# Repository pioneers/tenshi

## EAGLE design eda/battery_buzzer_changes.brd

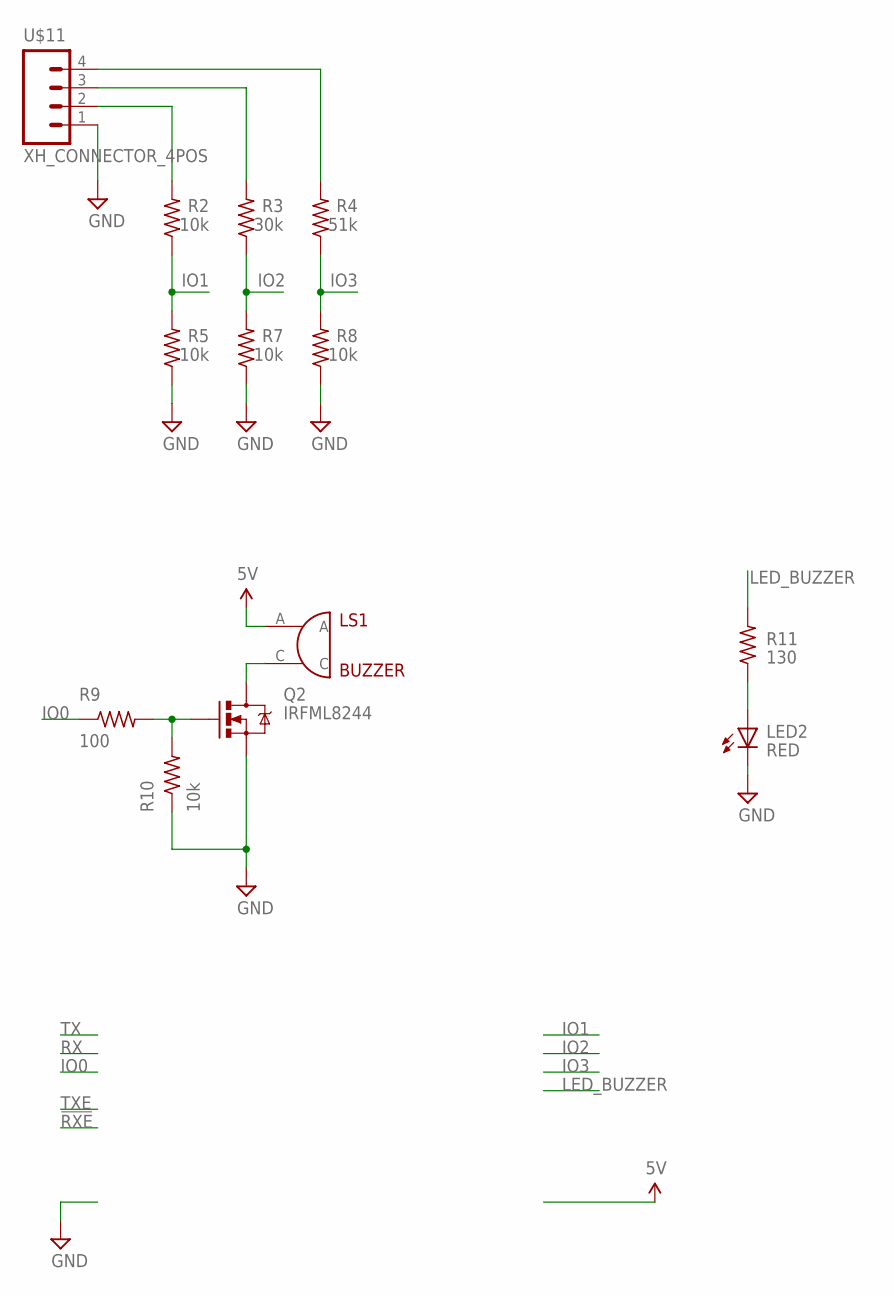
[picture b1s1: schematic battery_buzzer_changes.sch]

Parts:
LED2: RED; LED-0805
LS1: BUZZER; BUZZER_MAGNETIC_5V_12MM_RADIAL
Q2: IRFML8244; SOT23-3
R2, R5, R7, R8, R10: 10k; R0603
R3: 30k; R0603
R4: 51k; R0603
R9: 100; R0603
R11: 130; R0603
U$11: XH_CONNECTOR_4POS; XH_CONNECTOR_4POS_2.5MM

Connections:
5V: LS1.A
GND: LED2.C, Q2.2 (S), R5.1, R7.1, R8.1, R10.1, U$11.1
IO0: R9.1
IO1: R2.1, R5.2
IO2: R3.1, R7.2
IO3: R4.1, R8.2
LED_BUZZER: R11.2
unnamed: R2.2, U$11.2
unnamed: R3.2, U$11.3
unnamed: R4.2, U$11.4
unnamed: LS1.C, Q2.3 (D)
unnamed: Q2.1 (G), R9.2, R10.2
unnamed: LED2.A, R11.1

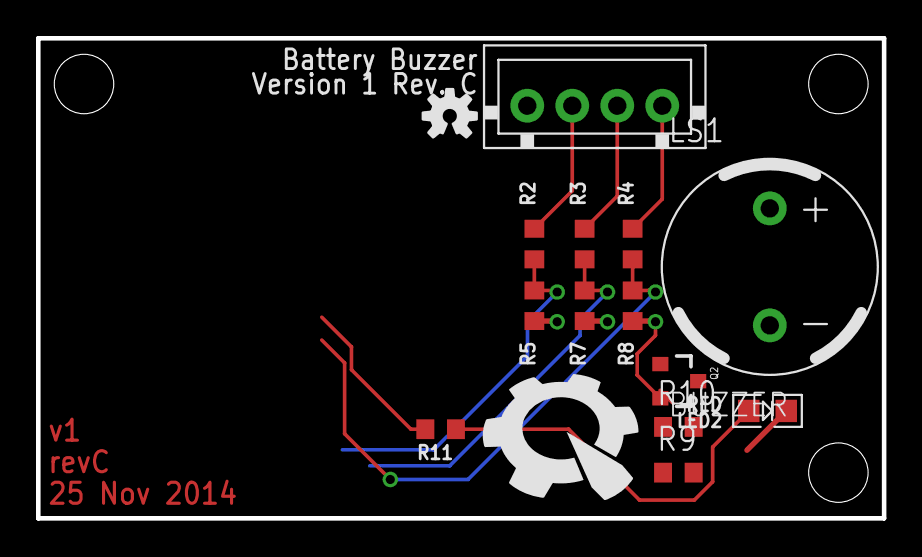
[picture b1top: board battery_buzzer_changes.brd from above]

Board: 2 copper layers, 47.0 x 26.7 mm, 18 parts (0 on the bottom side), 10 nets.

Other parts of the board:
U$1: PIE-LOGO-SMALL
U$7: OSHW-LOGO-S
U$8, U$9, U$17: STAND-OFF

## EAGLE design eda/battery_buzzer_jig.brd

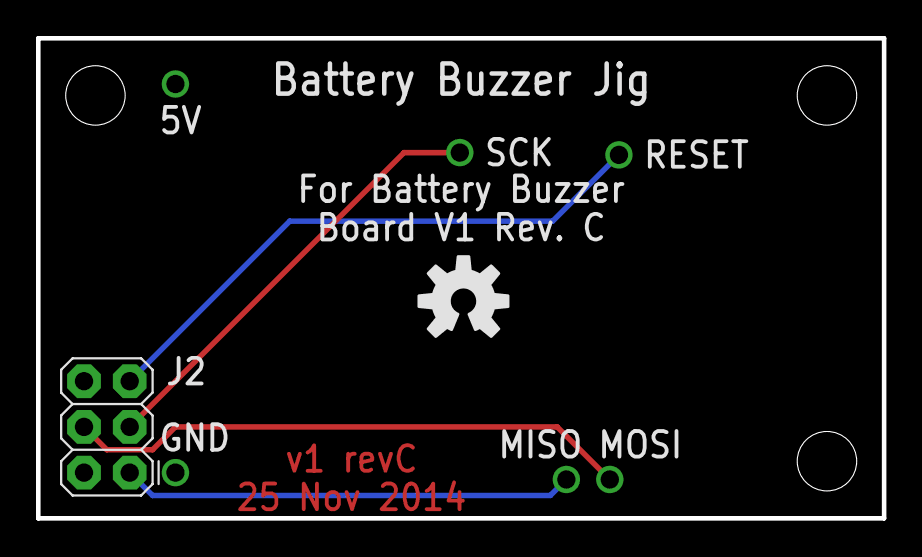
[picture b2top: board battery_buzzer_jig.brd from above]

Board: 2 copper layers, 47.0 x 26.7 mm, 12 parts (1 on the bottom side), 6 nets.

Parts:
5V: POGO_PIN_394
GND: POGO_PIN_394
J2: AVR_SPI_PRG_6PTH; 2X3
MISO: POGO_PIN_394
MOSI: POGO_PIN_394
RESET: POGO_PIN_394
SCK: POGO_PIN_394
U$1: OSHW-LOGO-M
U$2: PIE-LOGO-SMALL
U$3, U$4, U$5: STAND-OFF

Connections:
5V: 5V.POGO_PIN, J2.2
A: GND.POGO_PIN, J2.6
MISO: J2.1, MISO.POGO_PIN
MOSI: J2.4, MOSI.POGO_PIN
RESET: J2.5, RESET.POGO_PIN
SCK: J2.3, SCK.POGO_PIN

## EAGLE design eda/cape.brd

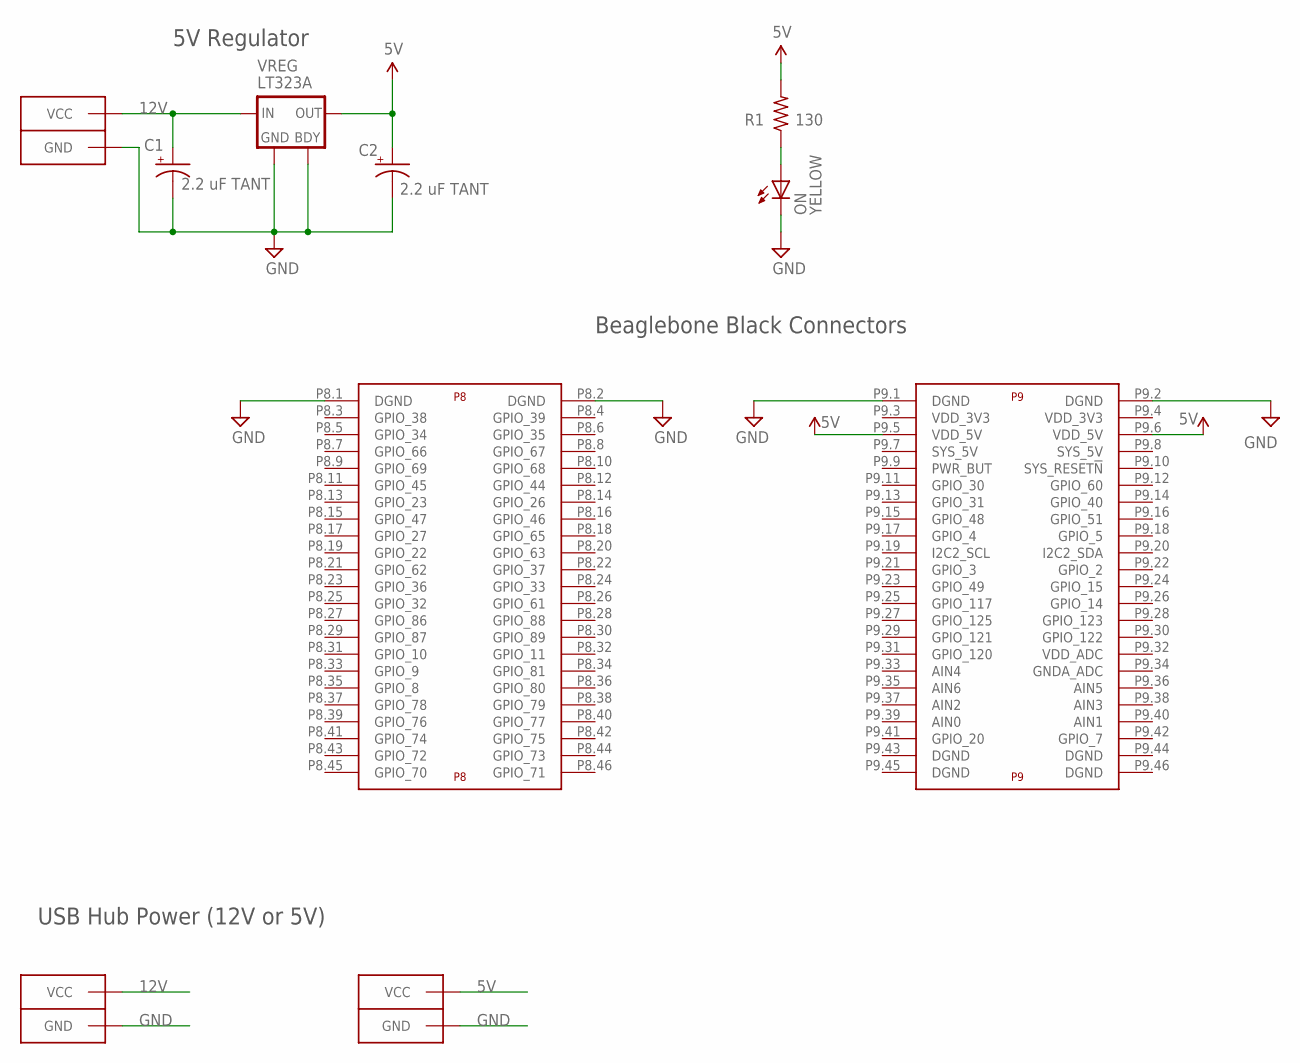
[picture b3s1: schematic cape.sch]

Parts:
BATT: 12V; ANDERSON_HORIZONTAL
C1, C2: 2.2 uF TANT; EIA3216
CAPE: BEAGLE_BONE_BLACK_CAPE
J2: 12V; POWER-WIRE
J3: 5V; POWER-WIRE
ON: YELLOW; LED-0805
R1: 130; R0603
VREG: LT323A; TO-220

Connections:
5V: C2.A (+), CAPE.P9.5 (VDD_5V), CAPE.P9.6 (VDD_5V), J3.VCC, R1.2, VREG.OUT
12V: BATT.PIN2 (VCC), BATT.PIN2-LEAD (VCC), C1.A (+), J2.VCC, VREG.IN
GND: BATT.PIN1 (GND), BATT.PIN1-LEAD (GND), C1.C (-), C2.C (-), CAPE.P8.1 (DGND), CAPE.P8.2 (DGND), CAPE.P9.1 (DGND), CAPE.P9.2 (DGND), J2.GND, J3.GND, ON.C, VREG.GND, VREG.PAD (BDY)
unnamed: ON.A, R1.1

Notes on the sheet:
Beaglebone Black Connectors
USB Hub Power (12V or 5V)
5V Regulator

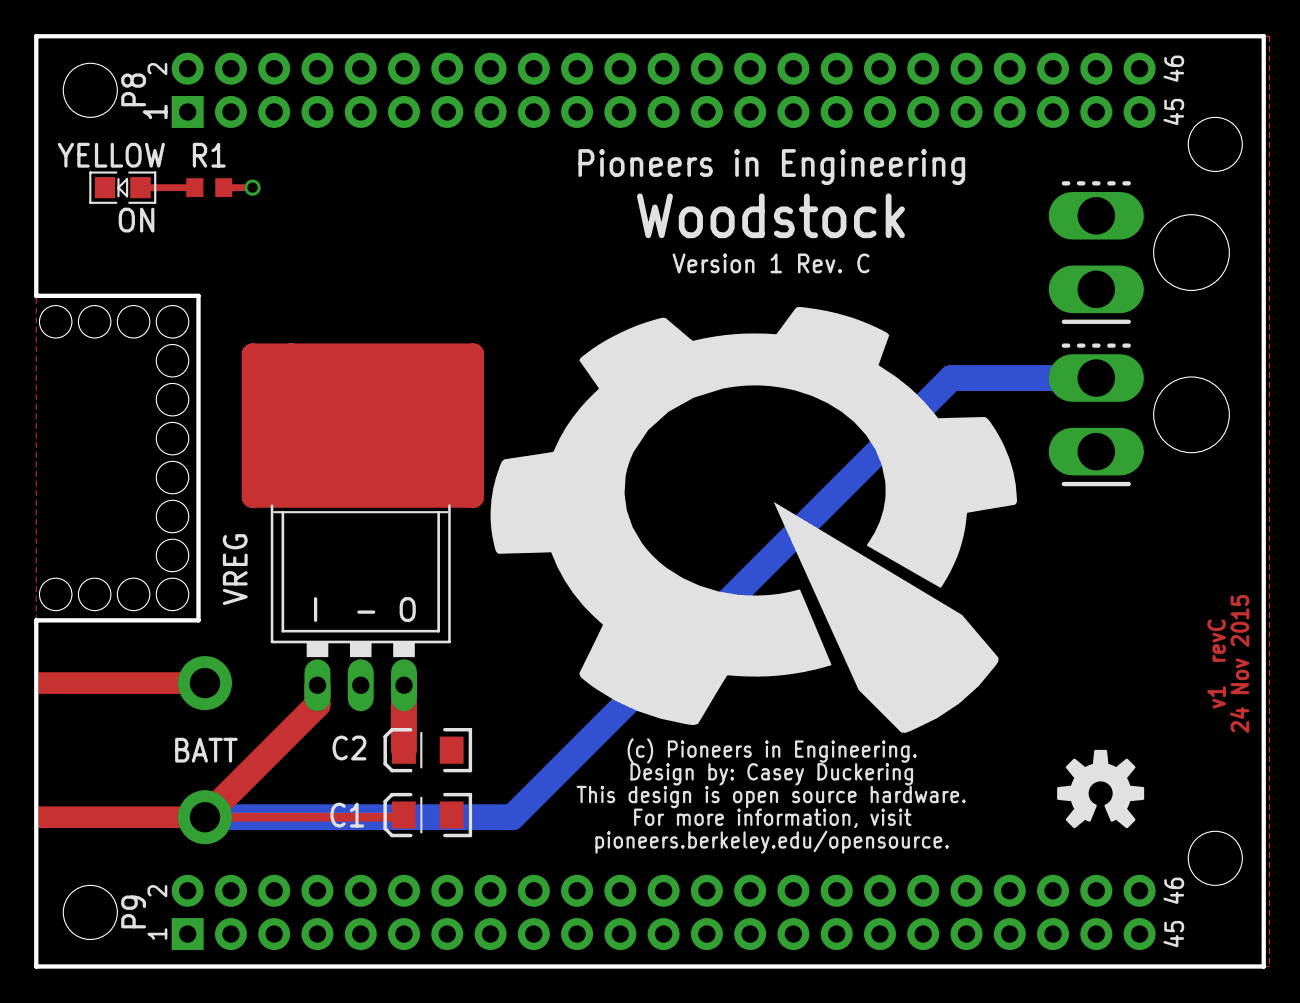
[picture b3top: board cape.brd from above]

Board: 2 copper layers, 72.1 x 54.6 mm, 11 parts (0 on the bottom side), 4 nets.

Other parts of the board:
U$3: OSHW-LOGO-M
U$6: PIE-LOGO

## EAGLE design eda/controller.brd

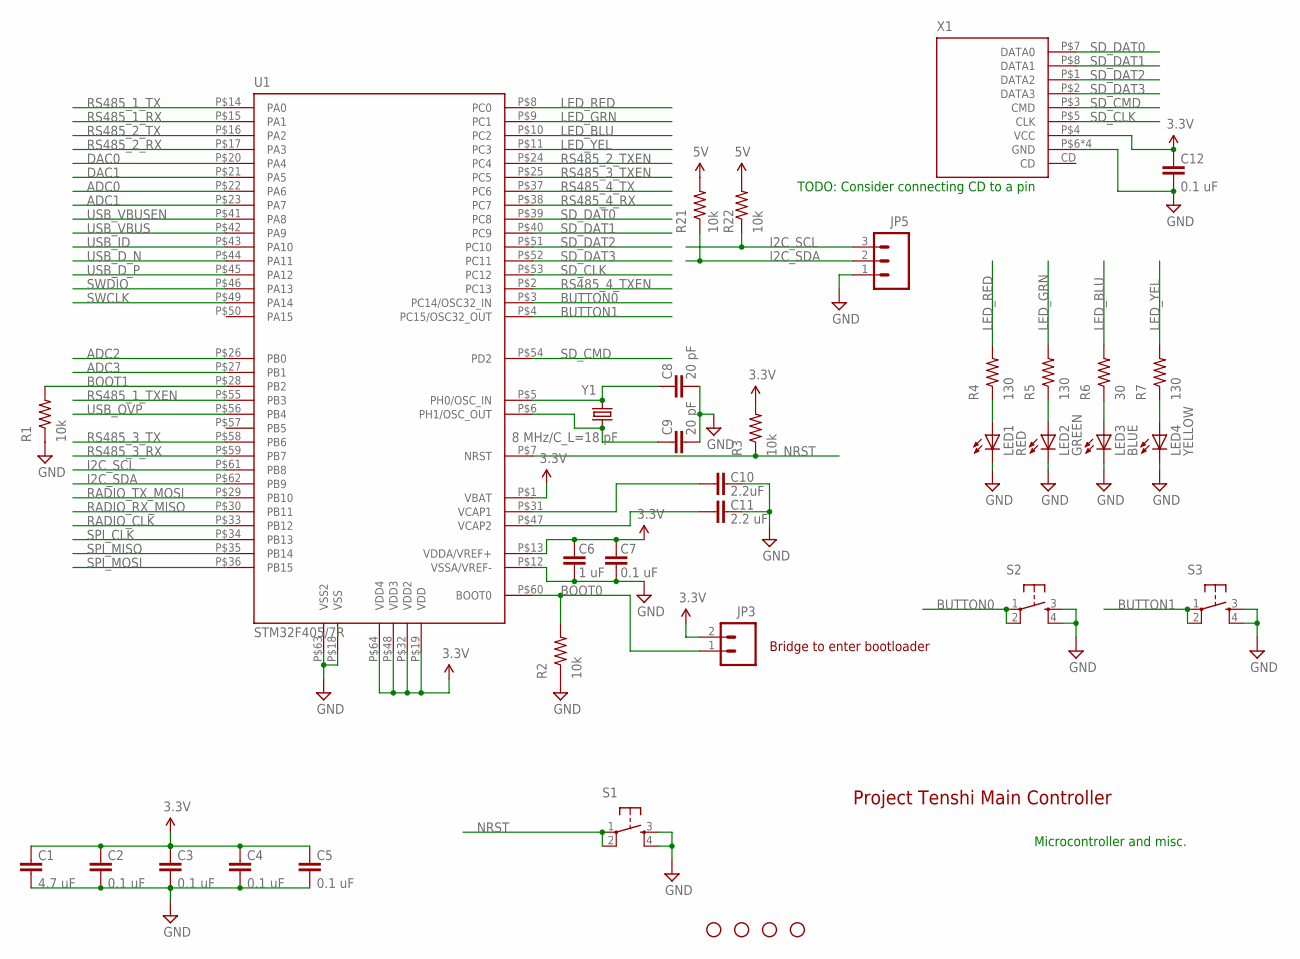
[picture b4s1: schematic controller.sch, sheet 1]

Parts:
C1: 4.7 uF; 0805
C2, C3, C4, C5, C7, C12: 0.1 uF; 0603-CAP
C6: 1 uF; 0603-CAP
C8, C9: 20 pF; 0603-CAP
C10: 2.2uF; 0603-CAP
C11: 2.2 uF; 0603-CAP
JP3: M02PTH; 1X02
JP5: M031X03-MTA; 1X03-MTA
LED1: RED; LED-0805
LED2: GREEN; LED-0805
LED3: BLUE; LED-0805
LED4: YELLOW; LED-0805
R1, R2, R3, R21, R22: 10k; R0603
R4, R5, R7: 130; R0603
R6: 30; R0603
S1, S2, S3: TAC_SWITCHPTH; TACTILE-PTH
STANDOFF1, STANDOFF2, STANDOFF3, STANDOFF4: STAND-OFF
U1: STM32F405/7R; QFP64
X1: MICROSD-SOCKETAMPHENOL; MICROSD-SOCKET
Y1: 8 MHz/C_L=18 pF; HC49UP

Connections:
3.3V: C1.1, C2.1, C3.1, C4.1, C5.1, C6.1, C7.1, C12.1, JP3.2, R3.2, U1.P$1 (VBAT), U1.P$13 (VDDA/VREF+), U1.P$19 (VDD), U1.P$32 (VDD2), U1.P$48 (VDD3), U1.P$64 (VDD4), X1.P$4 (VCC); also elsewhere on the board
5V: R21.2, R22.2; also elsewhere on the board
ADC0: U1.P$22 (PA6)
ADC1: U1.P$23 (PA7)
ADC2: U1.P$26 (PB0)
ADC3: U1.P$27 (PB1)
BOOT0: JP3.1, R2.2, U1.P$60 (BOOT0); also elsewhere on the board
BOOT1: R1.2, U1.P$28 (PB2)
BUTTON0: S2.1, S2.2, U1.P$3 (PC14/OSC32_IN)
BUTTON1: S3.1, S3.2, U1.P$4 (PC15/OSC32_OUT)
DAC0: U1.P$20 (PA4)
DAC1: U1.P$21 (PA5)
GND: C1.2, C2.2, C3.2, C4.2, C5.2, C6.2, C7.2, C8.2, C9.2, C10.2, C11.2, C12.2, JP5.1, LED1.C, LED2.C, LED3.C, LED4.C, R1.1, R2.1, S1.3, S1.4, S2.3, S2.4, S3.3, S3.4, U1.P$12 (VSSA/VREF-), U1.P$18 (VSS), U1.P$63 (VSS2), X1.P$6 (GND), X1.P$9 (GND), X1.P$10 (GND), X1.P$11 (GND); also elsewhere on the board
I2C_SCL: JP5.3, R22.1, U1.P$61 (PB8)
I2C_SDA: JP5.2, R21.1, U1.P$62 (PB9)
LED_BLU: R6.2, U1.P$10 (PC2)
LED_GRN: R5.2, U1.P$9 (PC1)
LED_RED: R4.2, U1.P$8 (PC0)
LED_YEL: R7.2, U1.P$11 (PC3)
unnamed: C11.1, U1.P$47 (VCAP2)
unnamed: C10.1, U1.P$31 (VCAP1)
unnamed: C9.1, U1.P$6 (PH1/OSC_OUT), Y1.1
unnamed: LED1.A, R4.1
unnamed: C8.1, U1.P$5 (PH0/OSC_IN), Y1.2
unnamed: LED2.A, R5.1
unnamed: LED3.A, R6.1
unnamed: LED4.A, R7.1
NRST: R3.1, S1.1, S1.2, U1.P$7 (NRST); also elsewhere on the board
RADIO_CLK: U1.P$33 (PB12); also elsewhere on the board
RADIO_RX_MISO: U1.P$30 (PB11); also elsewhere on the board
RADIO_TX_MOSI: U1.P$29 (PB10); also elsewhere on the board
RS485_1_RX: U1.P$15 (PA1); also elsewhere on the board
RS485_1_TX: U1.P$14 (PA0); also elsewhere on the board
RS485_1_TXEN: U1.P$55 (PB3); also elsewhere on the board
RS485_2_RX: U1.P$17 (PA3); also elsewhere on the board
RS485_2_TX: U1.P$16 (PA2); also elsewhere on the board
RS485_2_TXEN: U1.P$24 (PC4); also elsewhere on the board
RS485_3_RX: U1.P$59 (PB7); also elsewhere on the board
RS485_3_TX: U1.P$58 (PB6); also elsewhere on the board
RS485_3_TXEN: U1.P$25 (PC5); also elsewhere on the board
RS485_4_RX: U1.P$38 (PC7); also elsewhere on the board
RS485_4_TX: U1.P$37 (PC6); also elsewhere on the board
RS485_4_TXEN: U1.P$2 (PC13); also elsewhere on the board
SD_CLK: U1.P$53 (PC12), X1.P$5 (CLK)
SD_CMD: U1.P$54 (PD2), X1.P$3 (CMD)
SD_DAT0: U1.P$39 (PC8), X1.P$7 (DATA0)
SD_DAT1: U1.P$40 (PC9), X1.P$8 (DATA1)
SD_DAT2: U1.P$51 (PC10), X1.P$1 (DATA2)
SD_DAT3: U1.P$52 (PC11), X1.P$2 (DATA3)
SPI_CLK: U1.P$34 (PB13)
SPI_MISO: U1.P$35 (PB14)
SPI_MOSI: U1.P$36 (PB15)
SWCLK: U1.P$49 (PA14); also elsewhere on the board
SWDIO: U1.P$46 (PA13); also elsewhere on the board
USB_D_N: U1.P$44 (PA11); also elsewhere on the board
USB_D_P: U1.P$45 (PA12); also elsewhere on the board
USB_ID: U1.P$43 (PA10); also elsewhere on the board
USB_OVP: U1.P$56 (PB4); also elsewhere on the board
USB_VBUS: U1.P$42 (PA9); also elsewhere on the board
USB_VBUSEN: U1.P$41 (PA8); also elsewhere on the board

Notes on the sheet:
Project Tenshi Main Controller
Bridge to enter bootloader
TODO: Consider connecting CD to a pin
Microcontroller and misc.

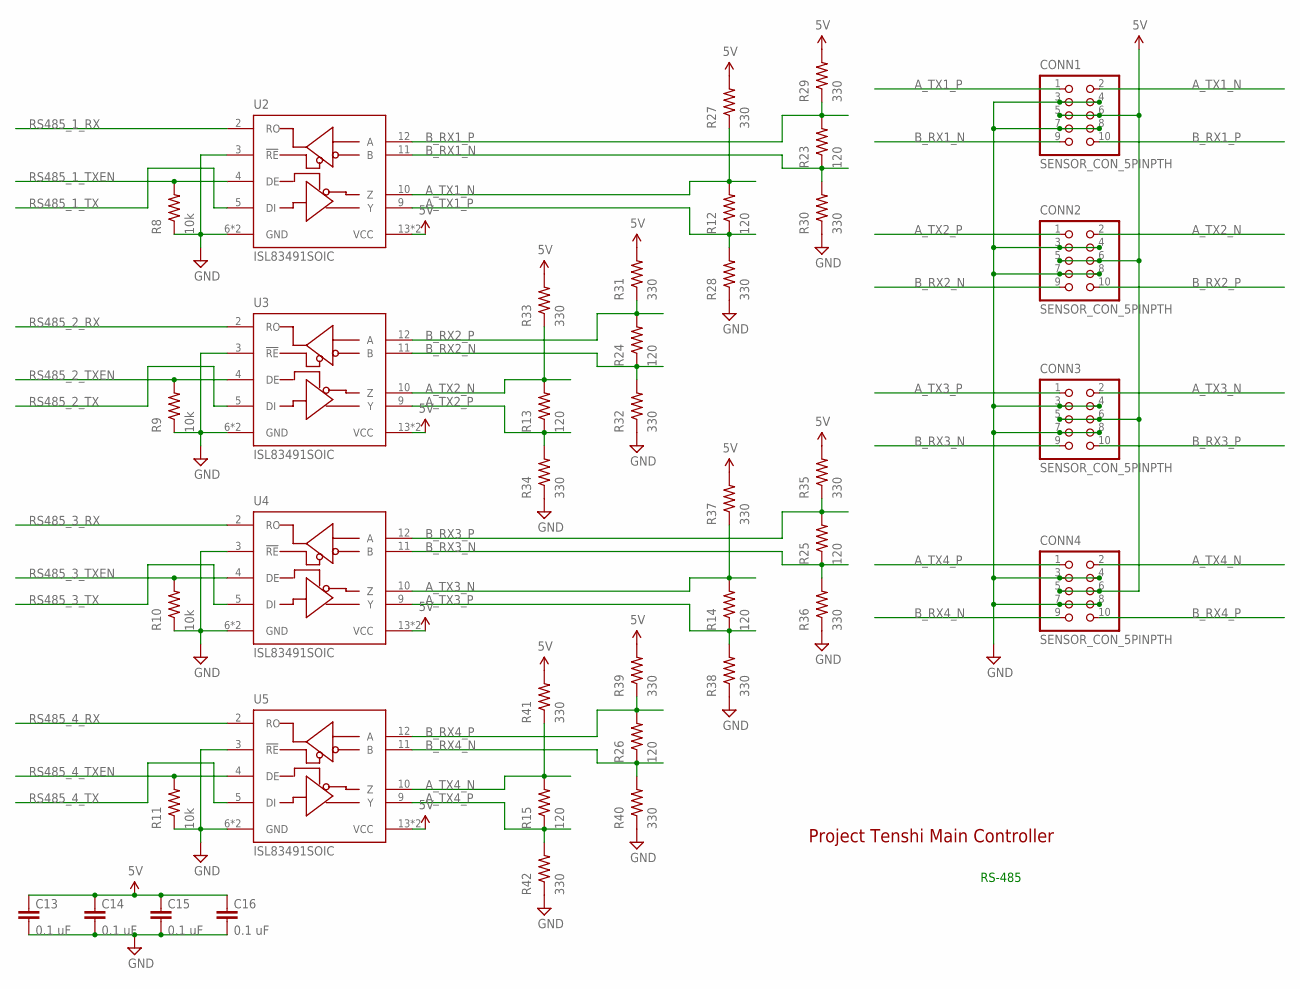
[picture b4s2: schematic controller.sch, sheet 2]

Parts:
C13, C14, C15, C16: 0.1 uF; 0603-CAP
CONN1, CONN2, CONN3, CONN4: SENSOR_CON_5PINPTH; 2X5_SHROUDED
R8, R9, R10, R11: 10k; R0603
R12, R13, R14, R15, R23, R24, R25, R26: 120; R0603
R27, R28, R29, R30, R31, R32, R33, R34, R35, R36, R37, R38, R39, R40, R41, R42: 330; R0603
U2, U3, U4, U5: ISL83491SOIC; SOIC14

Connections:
5V: C13.1, C14.1, C15.1, C16.1, CONN1.5, CONN1.6, CONN2.5, CONN2.6, CONN3.5, CONN3.6, CONN4.5, CONN4.6, R27.2, R29.2, R31.2, R33.2, R35.2, R37.2, R39.2, R41.2, U2.13 (VCC), U2.14 (VCC), U3.13 (VCC), U3.14 (VCC), U4.13 (VCC), U4.14 (VCC), U5.13 (VCC), U5.14 (VCC); also elsewhere on the board
A_TX1_N: CONN1.2, R12.2, R27.1, U2.10 (Z)
A_TX1_P: CONN1.1, R12.1, R28.2, U2.9 (Y)
A_TX2_N: CONN2.2, R13.2, R33.1, U3.10 (Z)
A_TX2_P: CONN2.1, R13.1, R34.2, U3.9 (Y)
A_TX3_N: CONN3.2, R14.2, R37.1, U4.10 (Z)
A_TX3_P: CONN3.1, R14.1, R38.2, U4.9 (Y)
A_TX4_N: CONN4.2, R15.2, R41.1, U5.10 (Z)
A_TX4_P: CONN4.1, R15.1, R42.2, U5.9 (Y)
B_RX1_N: CONN1.9, R23.1, R30.2, U2.11 (B)
B_RX1_P: CONN1.10, R23.2, R29.1, U2.12 (A)
B_RX2_N: CONN2.9, R24.1, R32.2, U3.11 (B)
B_RX2_P: CONN2.10, R24.2, R31.1, U3.12 (A)
B_RX3_N: CONN3.9, R25.1, R36.2, U4.11 (B)
B_RX3_P: CONN3.10, R25.2, R35.1, U4.12 (A)
B_RX4_N: CONN4.9, R26.1, R40.2, U5.11 (B)
B_RX4_P: CONN4.10, R26.2, R39.1, U5.12 (A)
GND: C13.2, C14.2, C15.2, C16.2, CONN1.3, CONN1.4, CONN1.7, CONN1.8, CONN2.3, CONN2.4, CONN2.7, CONN2.8, CONN3.3, CONN3.4, CONN3.7, CONN3.8, CONN4.3, CONN4.4, CONN4.7, CONN4.8, R8.1, R9.1, R10.1, R11.1, R28.1, R30.1, R32.1, R34.1, R36.1, R38.1, R40.1, R42.1, U2.3 (!RE), U2.6 (GND), U2.7 (GND), U3.3 (!RE), U3.6 (GND), U3.7 (GND), U4.3 (!RE), U4.6 (GND), U4.7 (GND), U5.3 (!RE), U5.6 (GND), U5.7 (GND); also elsewhere on the board
RS485_1_RX: U2.2 (RO); also elsewhere on the board
RS485_1_TX: U2.5 (DI); also elsewhere on the board
RS485_1_TXEN: R8.2, U2.4 (DE); also elsewhere on the board
RS485_2_RX: U3.2 (RO); also elsewhere on the board
RS485_2_TX: U3.5 (DI); also elsewhere on the board
RS485_2_TXEN: R9.2, U3.4 (DE); also elsewhere on the board
RS485_3_RX: U4.2 (RO); also elsewhere on the board
RS485_3_TX: U4.5 (DI); also elsewhere on the board
RS485_3_TXEN: R10.2, U4.4 (DE); also elsewhere on the board
RS485_4_RX: U5.2 (RO); also elsewhere on the board
RS485_4_TX: U5.5 (DI); also elsewhere on the board
RS485_4_TXEN: R11.2, U5.4 (DE); also elsewhere on the board

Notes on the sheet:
Project Tenshi Main Controller
RS-485

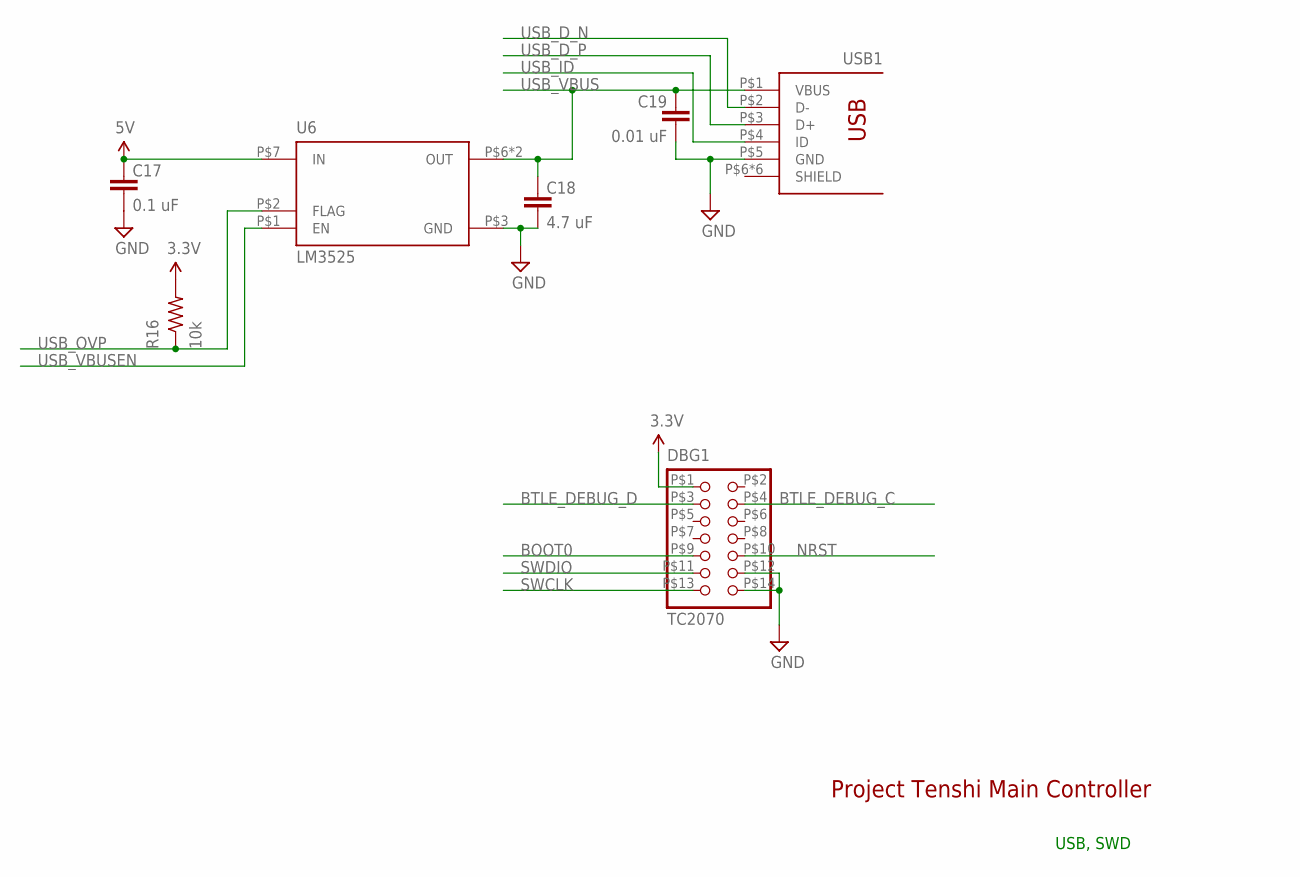
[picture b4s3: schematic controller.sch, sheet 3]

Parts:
C17: 0.1 uF; 0603-CAP
C18: 4.7 uF; 0805
C19: 0.01 uF; 0603-CAP
DBG1: TC2070
R16: 10k; R0603
U6: LM3525; SOIC8
USB1: USB-OTGMICRO-AB; USB-MICRO-AB

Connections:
3.3V: DBG1.P$1 (1), R16.2; also elsewhere on the board
5V: C17.1, U6.P$7 (IN); also elsewhere on the board
BOOT0: DBG1.P$9 (9); also elsewhere on the board
BTLE_DEBUG_C: DBG1.P$4 (4); also elsewhere on the board
BTLE_DEBUG_D: DBG1.P$3 (3); also elsewhere on the board
GND: C17.2, C18.2, C19.2, DBG1.P$12 (12), DBG1.P$14 (14), U6.P$3 (GND), USB1.P$5 (GND); also elsewhere on the board
NRST: DBG1.P$10 (10); also elsewhere on the board
SWCLK: DBG1.P$13 (13); also elsewhere on the board
SWDIO: DBG1.P$11 (11); also elsewhere on the board
USB_D_N: USB1.P$2 (D-); also elsewhere on the board
USB_D_P: USB1.P$3 (D+); also elsewhere on the board
USB_ID: USB1.P$4 (ID); also elsewhere on the board
USB_OVP: R16.1, U6.P$2 (FLAG); also elsewhere on the board
USB_VBUS: C18.1, C19.1, U6.P$6 (OUT), U6.P$8 (OUT), USB1.P$1 (VBUS); also elsewhere on the board
USB_VBUSEN: U6.P$1 (EN); also elsewhere on the board

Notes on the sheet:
USB, SWD
Project Tenshi Main Controller

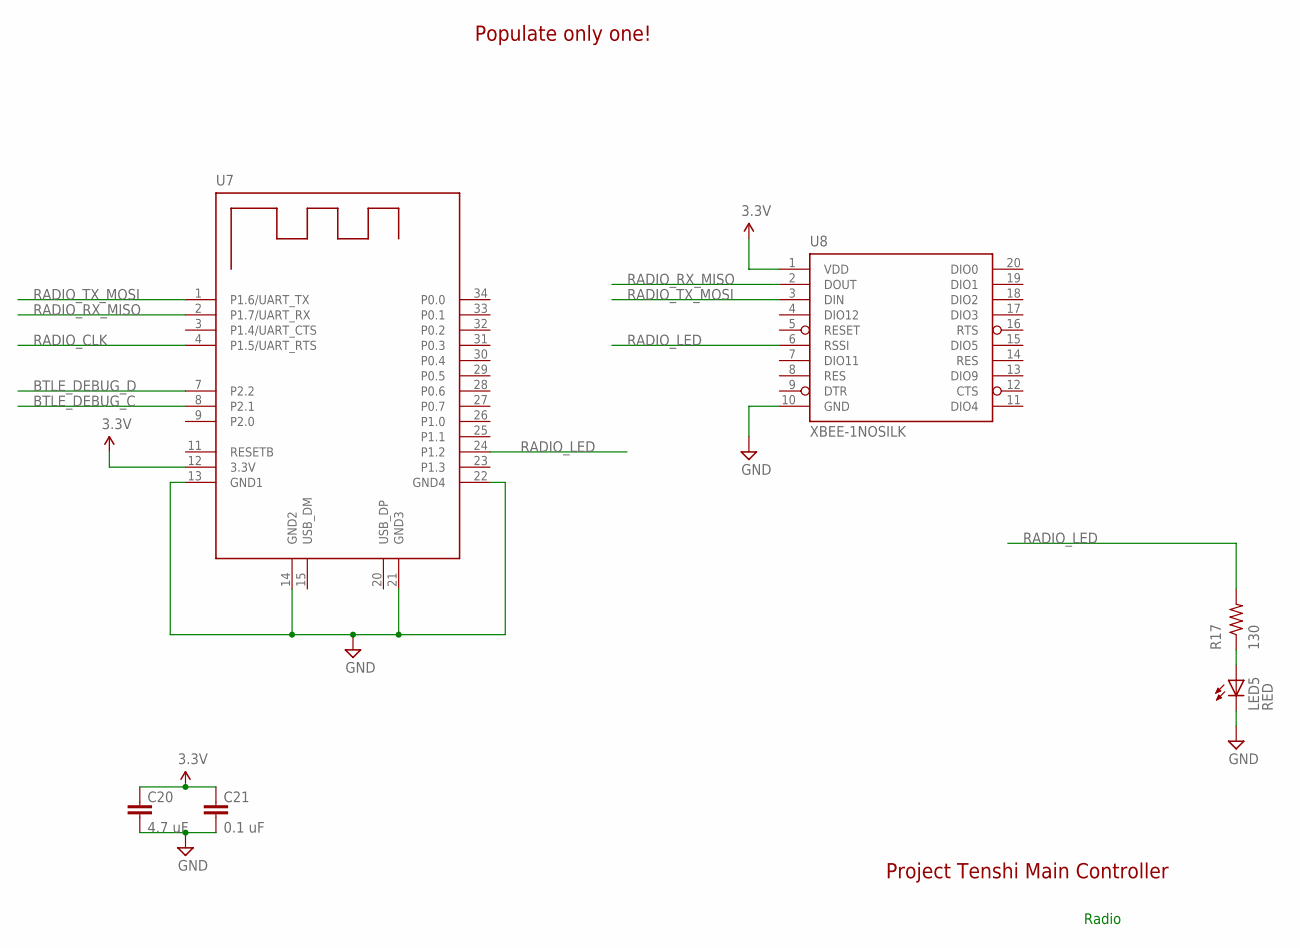
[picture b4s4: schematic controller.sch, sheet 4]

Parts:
C20: 4.7 uF; 0805
C21: 0.1 uF; 0603-CAP
LED5: RED; LED-0805
R17: 130; R0603
U7: BLE-HM-10
U8: XBEE-1NOSILK; XBEE-NOSILK

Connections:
3.3V: C20.1, C21.1, U7.12 (3.3V), U8.1 (VDD); also elsewhere on the board
BTLE_DEBUG_C: U7.8 (P2.1); also elsewhere on the board
BTLE_DEBUG_D: U7.7 (P2.2); also elsewhere on the board
GND: C20.2, C21.2, LED5.C, U7.13 (GND1), U7.14 (GND2), U7.21 (GND3), U7.22 (GND4), U8.10 (GND); also elsewhere on the board
unnamed: LED5.A, R17.1
RADIO_CLK: U7.4 (P1.5/UART_RTS); also elsewhere on the board
RADIO_LED: R17.2, U7.24 (P1.2), U8.6 (RSSI)
RADIO_RX_MISO: U7.2 (P1.7/UART_RX), U8.2 (DOUT); also elsewhere on the board
RADIO_TX_MOSI: U7.1 (P1.6/UART_TX), U8.3 (DIN); also elsewhere on the board

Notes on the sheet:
Populate only one!
Radio
Project Tenshi Main Controller

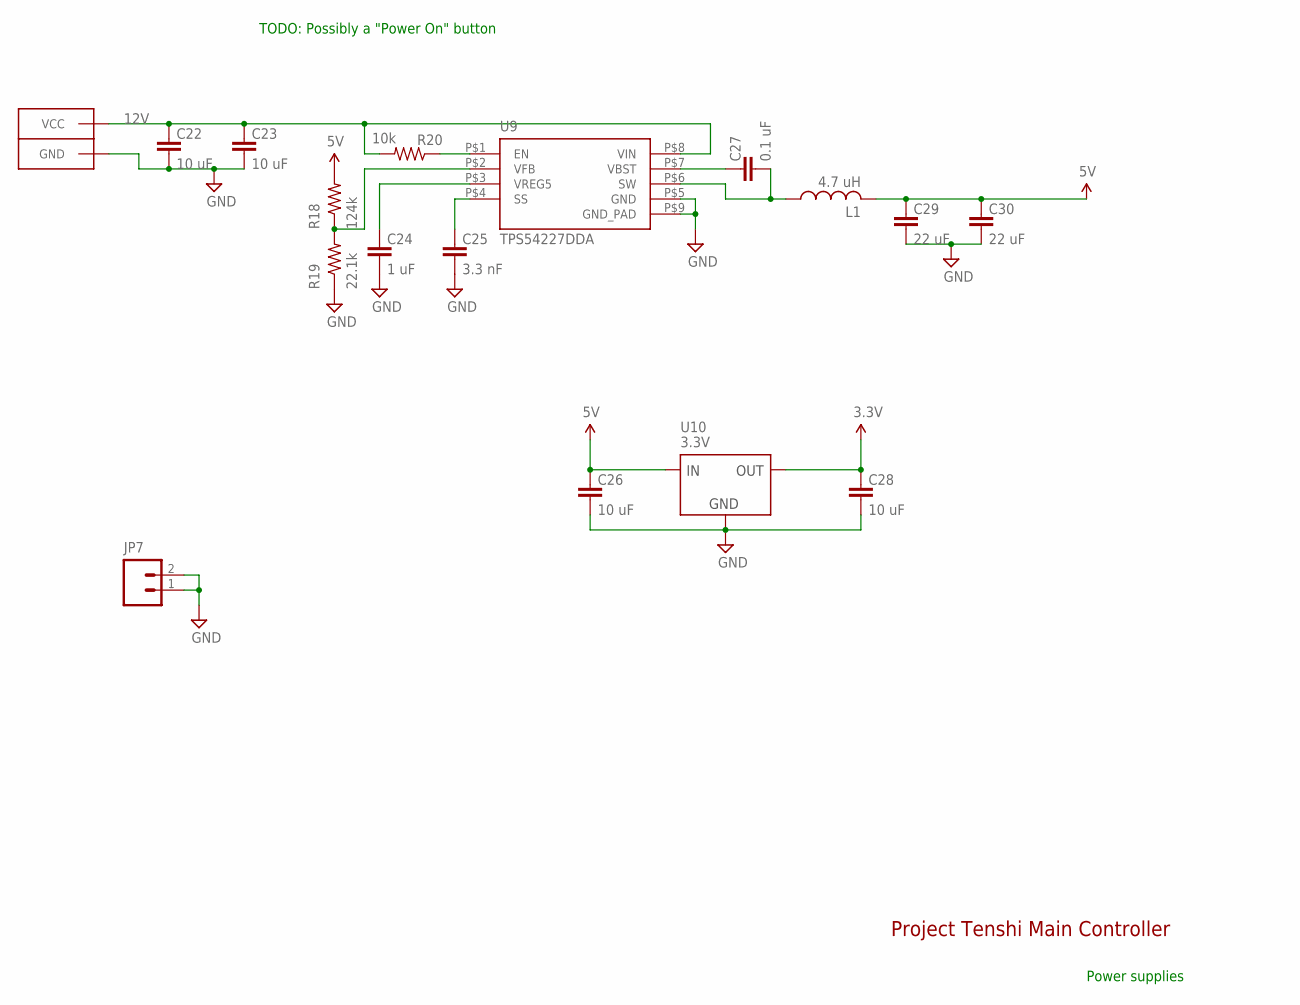
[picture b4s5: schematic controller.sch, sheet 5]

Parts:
C22, C23, C26, C28: 10 uF; 1206
C24: 1 uF; 0603-CAP
C25: 3.3 nF; 0603-CAP
C27: 0.1 uF; 0603-CAP
C29, C30: 22 uF; 1206
CONN5: ANDERSONHORIZONTAL; ANDERSON_HORIZONTAL
JP7: M02PTH; 1X02
L1: 4.7 uH; INDUCTOR-6MM
R18: 124k; R0603
R19: 22.1k; R0603
R20: 10k; R0603
U9: TPS54227DDA; DDA
U10: 3.3V; SOT223

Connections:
3.3V: C28.1, U10.P$2 (OUT), U10.P$4 (OUT); also elsewhere on the board
5V: C26.1, C29.1, C30.1, L1.P$2 (2), R18.2, U10.P$3 (IN); also elsewhere on the board
12V: C22.1, C23.1, CONN5.PIN2 (VCC), R20.2, U9.P$8 (VIN)
GND: C22.2, C23.2, C24.2, C25.2, C26.2, C28.2, C29.2, C30.2, CONN5.PIN1 (GND), JP7.1, JP7.2, R19.1, U9.P$5 (GND), U9.P$9 (GND_PAD), U10.P$1 (GND); also elsewhere on the board
unnamed: C27.1, U9.P$7 (VBST)
unnamed: C25.1, U9.P$4 (SS)
unnamed: C24.1, U9.P$3 (VREG5)
unnamed: R18.1, R19.2, U9.P$2 (VFB)
unnamed: R20.1, U9.P$1 (EN)
unnamed: C27.2, L1.P$1 (1), U9.P$6 (SW)

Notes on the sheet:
Project Tenshi Main Controller
Power supplies
TODO: Possibly a "Power On" button

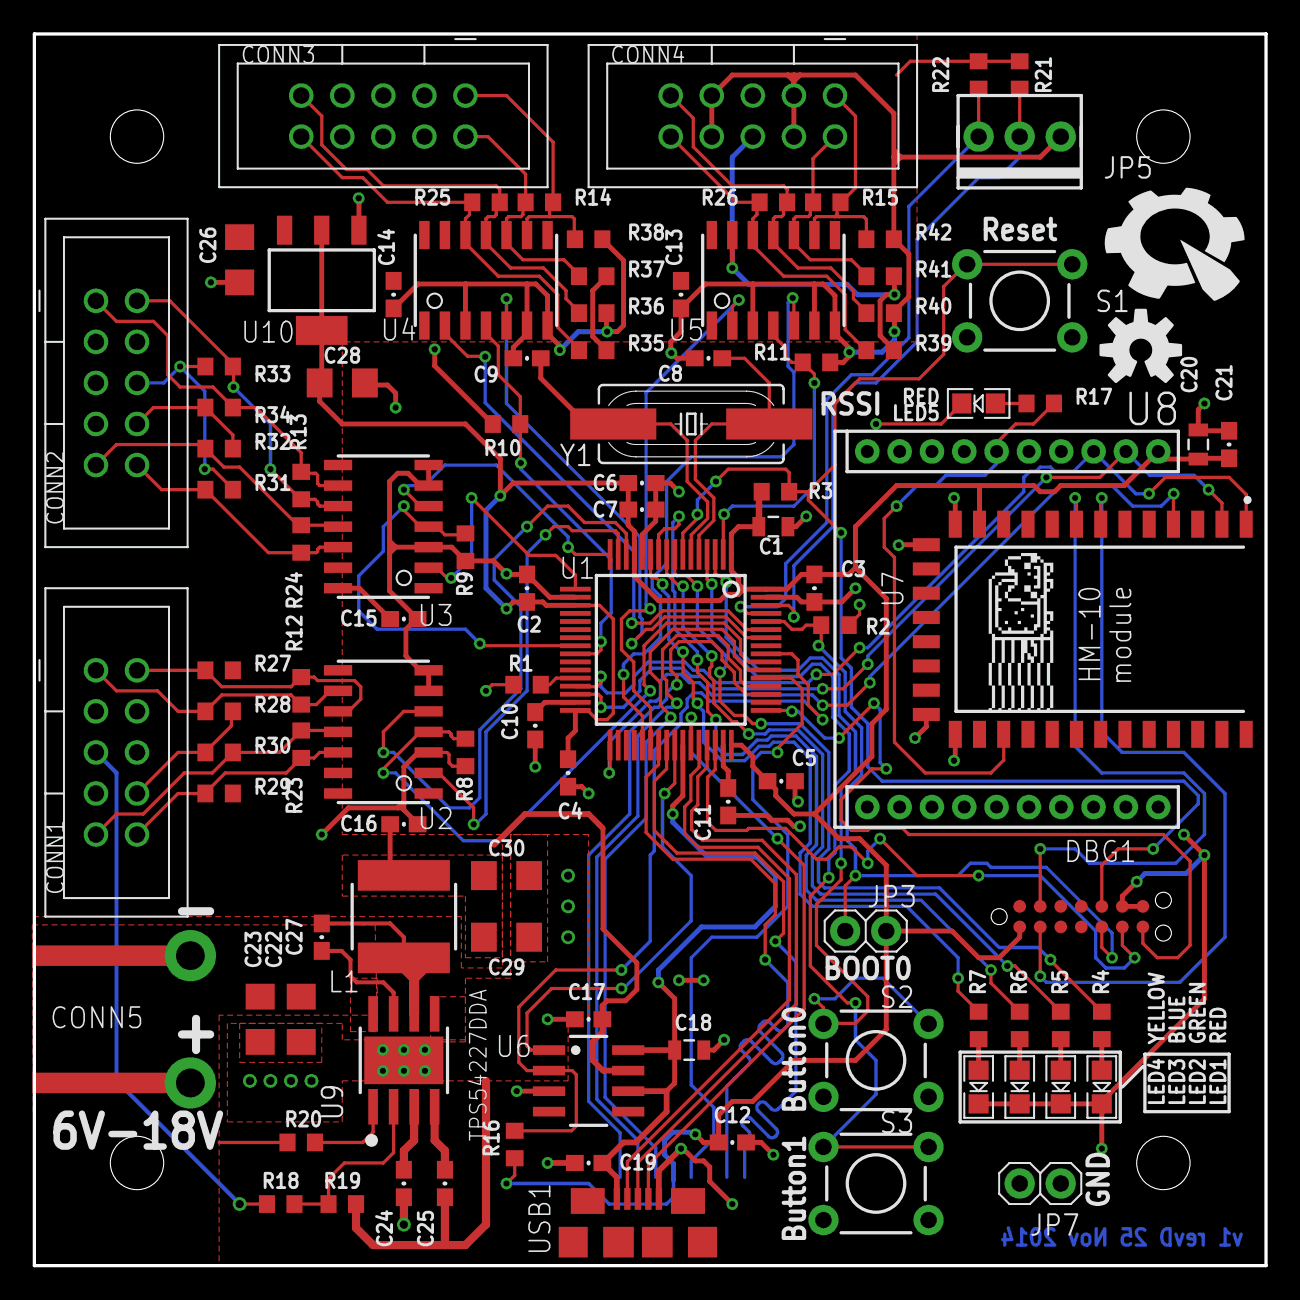
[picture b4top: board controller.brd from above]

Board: 2 copper layers, 76.2 x 76.2 mm, 110 parts (1 on the bottom side), 78 nets.

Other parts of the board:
U$13: NYAN-1CM
U$14: OSHW-LOGO-M
U$15: PIE-LOGO-SMALL

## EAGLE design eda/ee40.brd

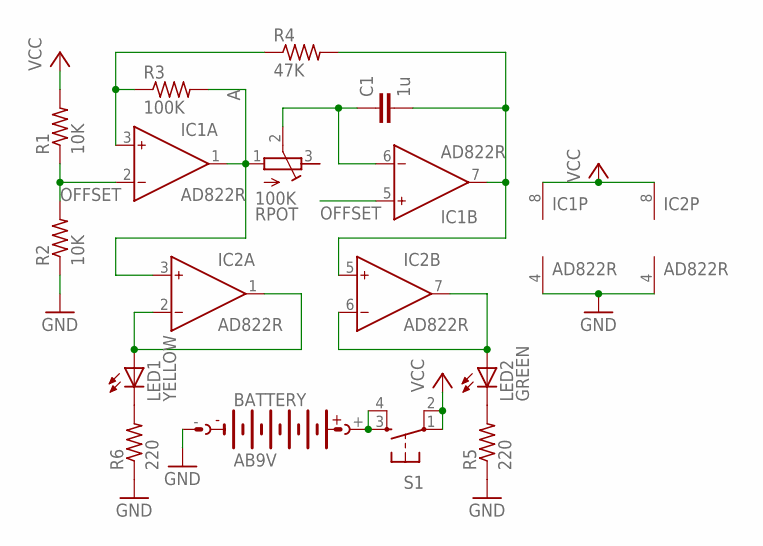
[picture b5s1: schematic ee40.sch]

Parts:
BATTERY: AB9V
C1: 1u; 0805
IC1, IC2: AD822R; SO8
LED1: YELLOW; LED3MM
LED2: GREEN; LED3MM
R1, R2: 10K; R0603
R3: 100K; R0603
R4: 47K; R0603
R5, R6: 220; R0603
RPOT: 100K; RTRIM5X
S1: TAC_SWITCHPTH; TACTILE-PTH

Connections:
A: IC1.1 (OUT), IC2.3 (IN+), R3.2, RPOT.1 (E)
B: IC2.6 (IN-), IC2.7 (OUT), LED2.A
GND: BATTERY.-, IC1.4 (V-), IC2.4 (V-), R2.1, R5.1, R6.1
unnamed: BATTERY.+, S1.3, S1.4
unnamed: C1.1, IC1.6 (IN-), RPOT.2 (S)
unnamed: C1.2, IC1.7 (OUT), IC2.5 (IN+), R4.2
unnamed: IC1.3 (IN+), R3.1, R4.1
unnamed: IC2.1 (OUT), IC2.2 (IN-), LED1.A
unnamed: LED1.K (C), R6.2
unnamed: LED2.K (C), R5.2
OFFSET: IC1.2 (IN-), IC1.5 (IN+), R1.1, R2.2
VCC: IC1.8 (V+), IC2.8 (V+), R1.2, S1.1, S1.2

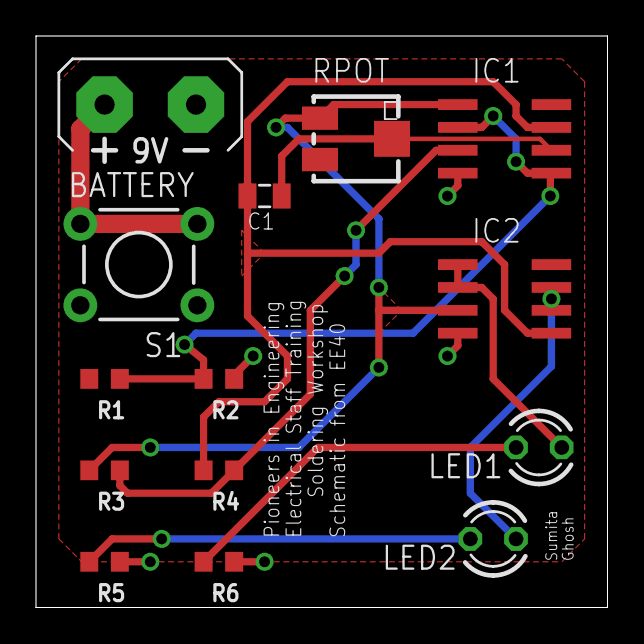
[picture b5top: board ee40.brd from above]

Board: 2 copper layers, 31.8 x 31.8 mm, 15 parts (1 on the bottom side), 12 nets.

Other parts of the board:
U$1: PIE-LOGO

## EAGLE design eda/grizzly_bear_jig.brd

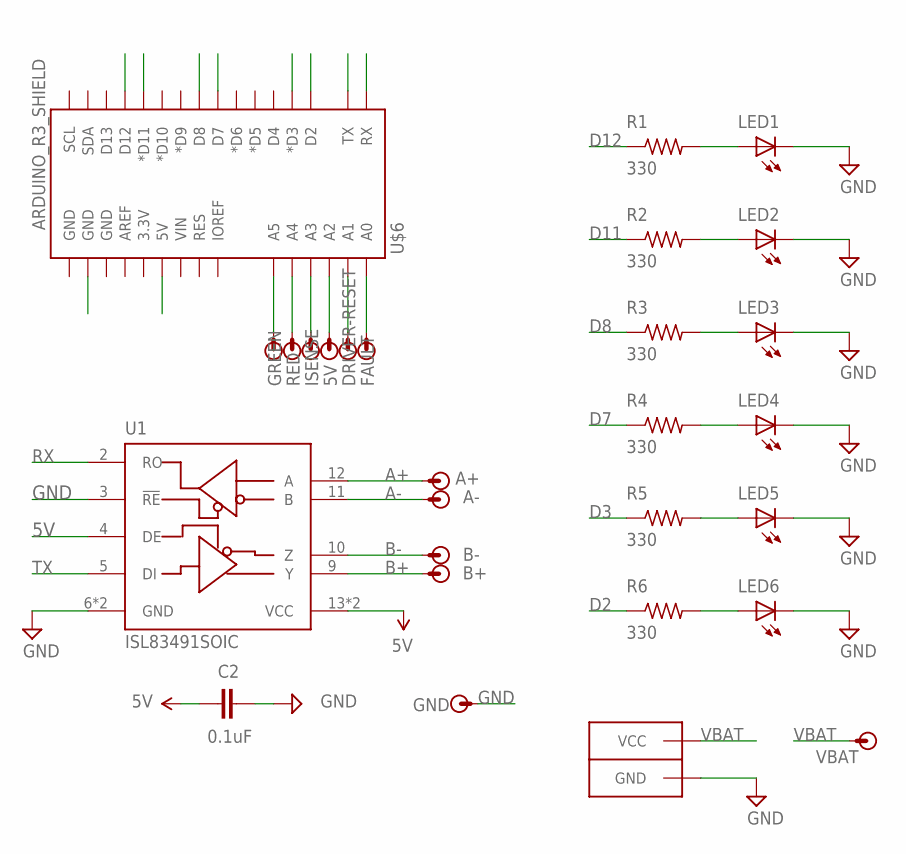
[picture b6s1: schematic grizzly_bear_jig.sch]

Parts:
5V: POGO_PIN; POGO_PIN_394
A+: POGO_PIN; POGO_PIN_394
A-: POGO_PIN; POGO_PIN_394
B+: POGO_PIN; POGO_PIN_394
B-: POGO_PIN; POGO_PIN_394
C2: 0.1uF; 0603-CAP
CONN1: ANDERSONHORIZONTAL; ANDERSON_HORIZONTAL
DRIVER-RESET: POGO_PIN; POGO_PIN_394
FAULT: POGO_PIN; POGO_PIN_394
GND: POGO_PIN; POGO_PIN_394
GREEN: POGO_PIN; POGO_PIN_394
ISENSE: POGO_PIN; POGO_PIN_394
LED1, LED2, LED3, LED4, LED5, LED6: LED0805; LED-0805
R1, R2, R3, R4, R5, R6: 330; R0603
RED: POGO_PIN; POGO_PIN_394
U1: ISL83491SOIC; SOIC14
U$6: ARDUINO_R3_SHIELD; UNO_R3_SHIELD
VBAT: POGO_PIN; POGO_PIN_394

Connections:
5V: C2.1, U1.4 (DE), U1.13 (VCC), U1.14 (VCC), U$6.5V
A+: A+.POGO_PIN, U1.12 (A)
A-: A-.POGO_PIN, U1.11 (B)
B+: B+.POGO_PIN, U1.9 (Y)
B-: B-.POGO_PIN, U1.10 (Z)
D2: R6.1, U$6.D2
D3: R5.1, U$6.D3 (*D3)
D7: R4.1, U$6.D7
D8: R3.1, U$6.D8
D11: R2.1, U$6.D11 (*D11)
D12: R1.1, U$6.D12
GND: C2.2, CONN1.PIN1 (GND), GND.POGO_PIN, LED1.C, LED2.C, LED3.C, LED4.C, LED5.C, LED6.C, U1.3 (!RE), U1.6 (GND), U1.7 (GND), U$6.GND@1 (GND)
unnamed: LED5.A, R5.2
unnamed: LED6.A, R6.2
unnamed: GREEN.POGO_PIN, U$6.A5
unnamed: RED.POGO_PIN, U$6.A4
unnamed: ISENSE.POGO_PIN, U$6.A3
unnamed: 5V.POGO_PIN, U$6.A2
unnamed: DRIVER-RESET.POGO_PIN, U$6.A1
unnamed: LED1.A, R1.2
unnamed: LED2.A, R2.2
unnamed: LED3.A, R3.2
unnamed: LED4.A, R4.2
unnamed: FAULT.POGO_PIN, U$6.A0
RX: U1.2 (RO), U$6.RX
TX: U1.5 (DI), U$6.TX
VBAT: CONN1.PIN2 (VCC), VBAT.POGO_PIN

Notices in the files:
parts and their libraries:
SparkFun-Boards: Licensing: Creative Commons ShareAlike 4.0 International - https://creativecommons.org/licenses/by-sa/4.0
